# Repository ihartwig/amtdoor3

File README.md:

AMT Door 3
==========

This repository houses hardware for the 3rd generation smart lock at Ace Monster Toys in Berkeley, CA. The hardware and software in this repo plus the PoEPi Hat make a single-cable solution for network connected locks.

</img>

## Features

* Wide Operation Buck Boost and Automation pHat (WOBBApHAT)
  * RPi Zero-sized pHAT
  * bi-directional level shifting for RFID Reader I/O (UART), PWM, and switch inputs (GPIO)
  * 12-24V strike power from on-board boost or aux input
  * (optionally) 5V RPi power from 12-24V source
  * order at http://dirtypcbs.com/store/designer/details/9832/5763/wobbaphat-for-amtdoor3

## Development Structure

* **docs**: Documentation used in designs.
* **pcb**: WOBBApHAT board to connect RPi Zero with RFID Reader and door strike.

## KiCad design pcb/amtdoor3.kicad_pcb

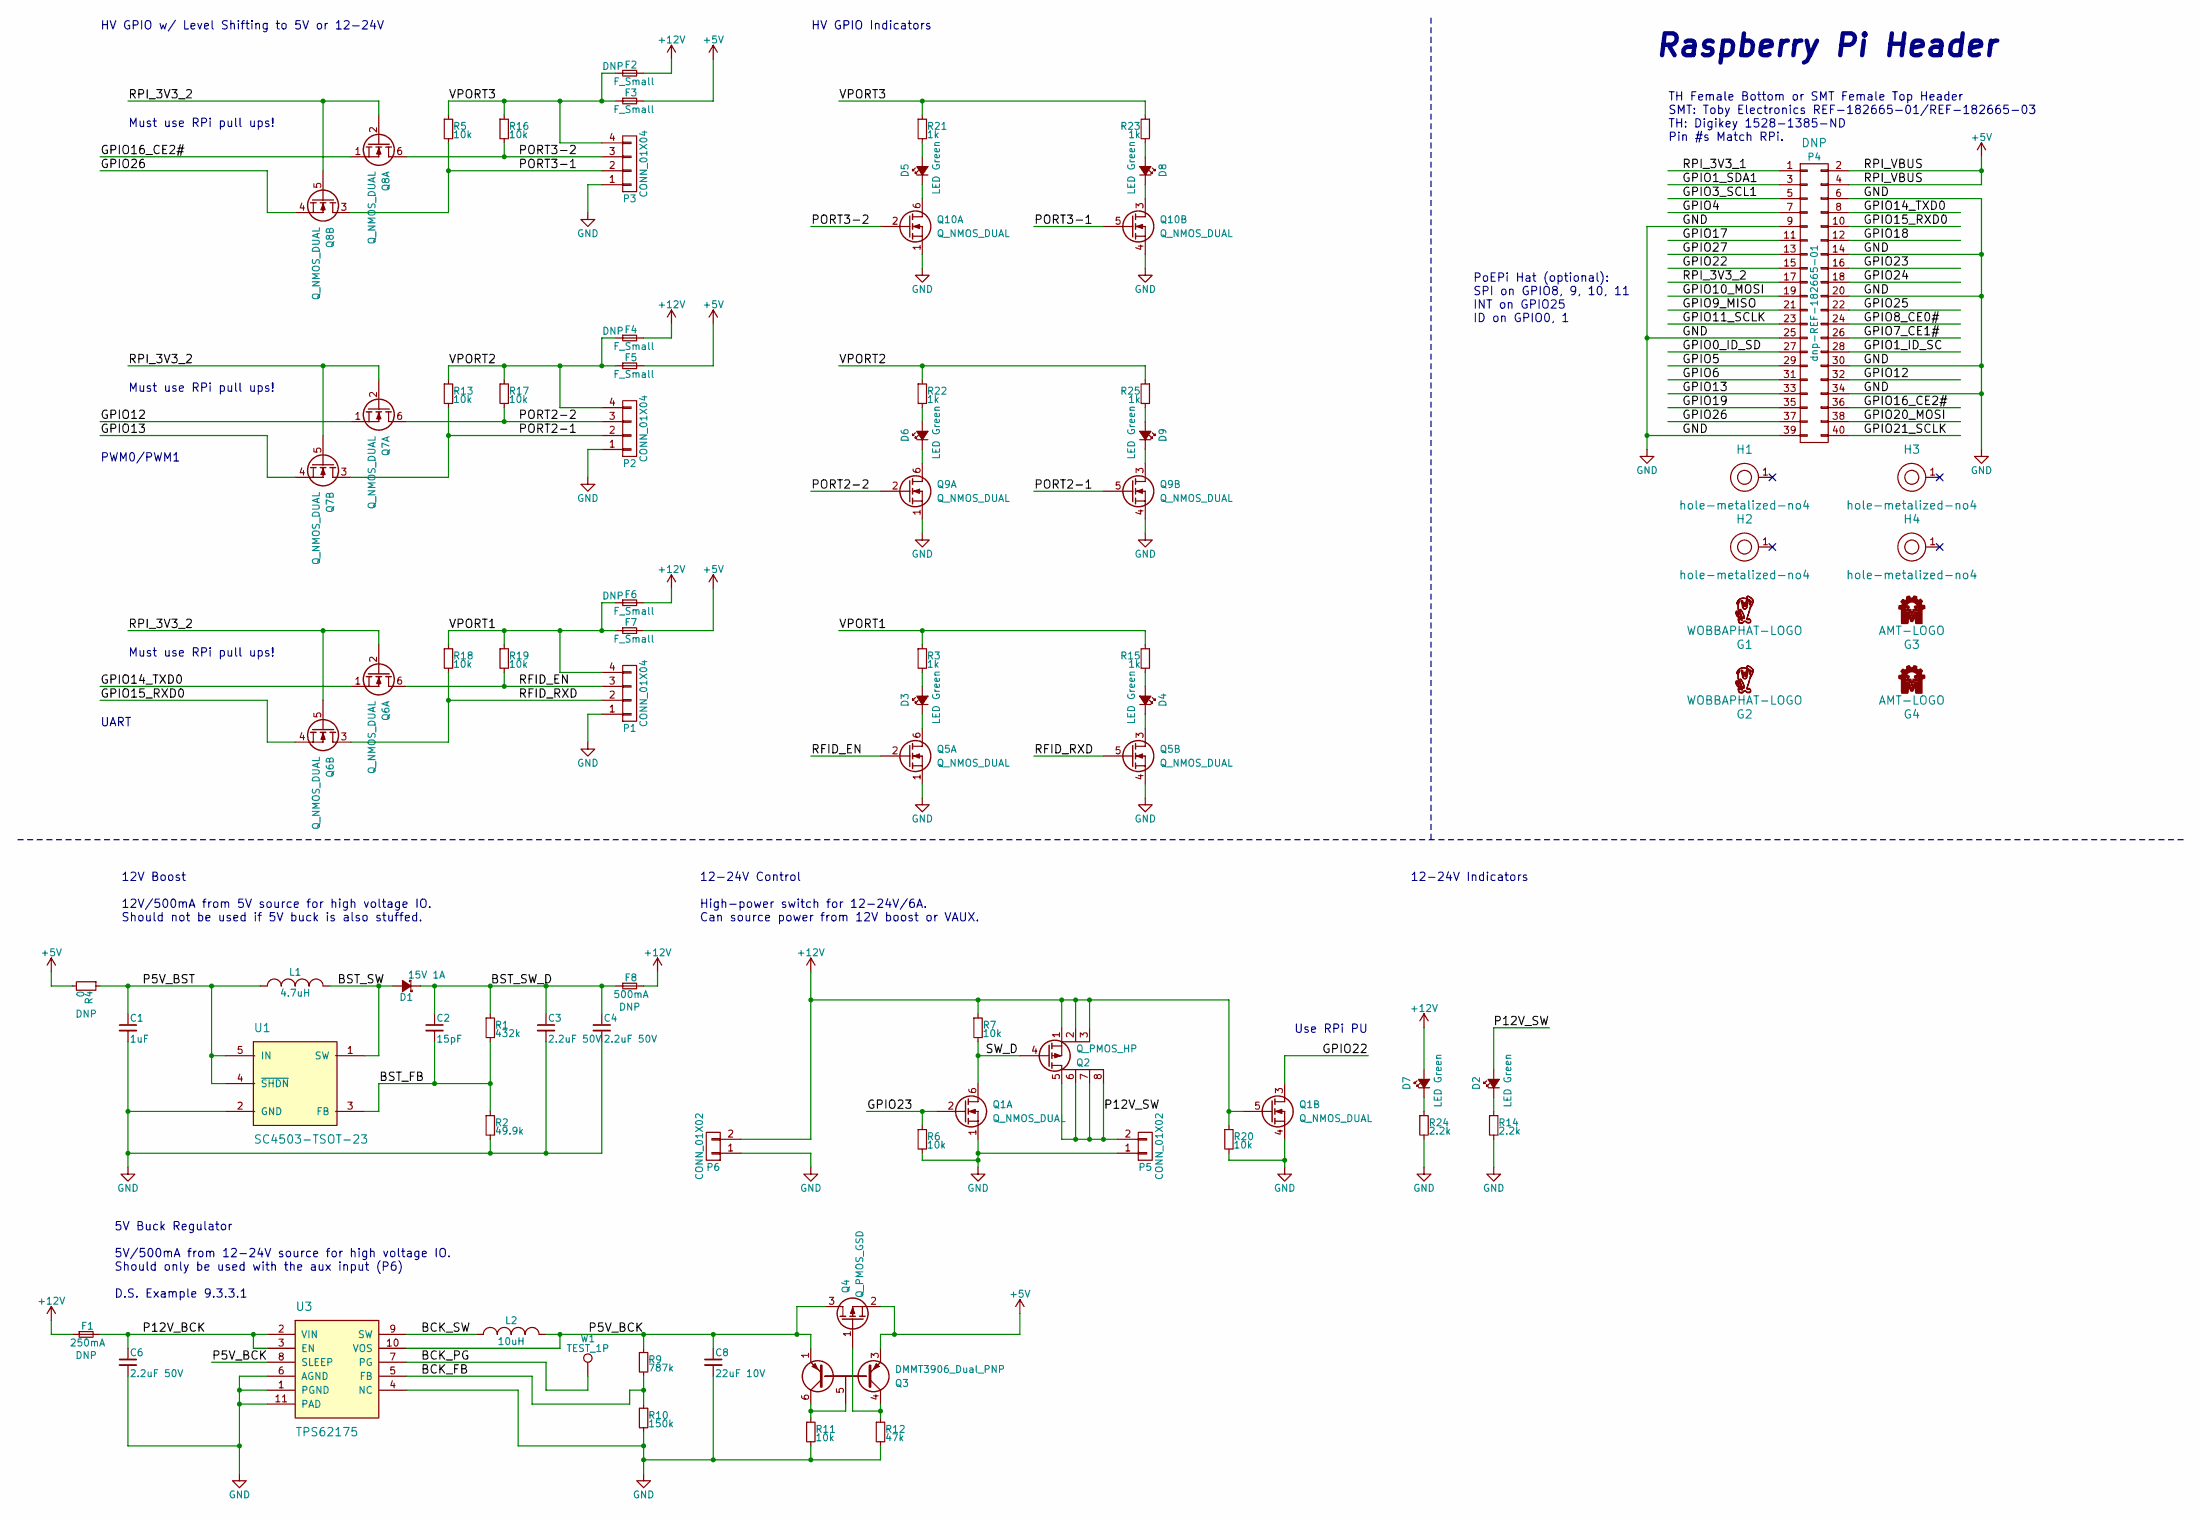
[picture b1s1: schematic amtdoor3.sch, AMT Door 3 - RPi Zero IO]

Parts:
C1: 1uF; C_0603
C2: 15pF; C_0603
C3, C4, C6: 2.2uF 50V; C_0805
C8: 22uF 10V; C_0805
D1: 15V 1A; SMB_Standard; Mfg Part No VS-10BQ015-M3/5BT; Digikey Part No VS-10BQ015-M3/5BTGICT-ND
D2, D3, D4, D5, D6, D7, D8, D9: LED Green; LED_0603; Mfg Part No LTST-C190GKT; Digikey Part No 160-1183-1-ND
F1: 250mA; R_0805
F2, F3, F4, F5, F6, F7: F_Small; R_0603
F8: 500mA; R_0805
G1: WOBBAPHAT-LOGO; wobbaphat-logo-fcu
G2: WOBBAPHAT-LOGO; wobbaphat-logo-fsilk-lg
G3: AMT-LOGO; amt-logo-fcu
G4: AMT-LOGO; amt-logo-fsilk-lg
H1, H2, H3, H4: hole-metalized-no4; hole-m3
L1: 4.7uH; Choke_SMD_Wuerth-WE-PD2-Typ-L; Mfg Part No NR6028T4R7M; Digikey Part No 587-2100-1-ND
L2: 10uH; Choke_SMD_Wuerth-WE-PD2-Typ-L; Mfg Part No NR6045T100M; Digikey Part No 587-2081-1-ND
P1, P2, P3: CONN_01X04; Socket_Strip_Straight_1x04
P4: dnp-REF-182665-01; Pin_Header_Straight_TH-SMT-NoPaste_2x20
P5, P6: CONN_01X02; Pin_Header_Straight_1x02_Pitch3.5mm; Mfg Part No OSTTE020104; Digikey Part No ED2740-ND
Q1, Q5, Q6, Q7, Q8, Q9, Q10: Q_NMOS_DUAL; SOT-23-6
Q2: Q_PMOS_HP; SOIC-8_3.9x4.9mm_Pitch1.27mm; Mfg Part No DMG4435SSS-13; Digikey Part No DMG4435SSS-13DICT-ND
Q3: DMMT3906_Dual_PNP; SOT-23-6; Mfg Part No DMMT3906-7-F; Digikey Part No DMMT3906-7-FDICT-ND
Q4: Q_PMOS_GSD; SOT-23; Mfg Part No DMP3099L-7; Digikey Part No DMP3099L-7DICT-ND
R1: 432k; R_0603
R2: 49.9k; R_0603
R3, R15, R21, R22, R23, R25: 1k; R_0603
R4: 0; R_0603
R5, R6, R7, R11, R13, R16, R17, R18, R19, R20: 10k; R_0603
R9: 787k; R_0603
R10: 150k; R_0603
R12: 47k; R_0603
R14, R24: 2.2k; R_0603
U1: SC4503-TSOT-23; SOT-23-5; Mfg Part No SC4503TSKTRT; Digikey Part No SC4503TSKCT-ND
U3: TPS62175; DFN-10-1EP_2x3mm_Pitch0.5mm; Mfg Part No todo; Digikey Part No todo
W1: TEST_1P; Measurement_Point_Round-SMD-Pad_Small

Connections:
+5V: F3.2, F5.2, F7.2, P4.2, P4.4, Q3.3 (E2), Q4.2 (S), R4.2
+12V: D7.2 (A), F1.1, F2.2, F4.2, F6.2, F8.2, P6.2, Q1.5 (G), Q2.1 (S), Q2.2 (S), Q2.3 (S), R7.1, R20.1
/BCK_FB: R9.2, R10.1, U3.5 (FB)
/BCK_PG: U3.7 (PG), W1.1
/BCK_SW: L2.1, U3.9 (SW)
/BST_FB: C2.2, R1.2, R2.1, U1.3 (FB)
/BST_SW: D1.2 (A), L1.2, U1.1 (SW)
/BST_SW_D: C2.1, C3.1, C4.1, D1.1 (K), F8.1, R1.1
/GPIO0_ID_SD: P4.27
/GPIO1_ID_SC: P4.28
/GPIO1_SDA1: P4.3
/GPIO3_SCL1: P4.5
/GPIO4: P4.7
/GPIO5: P4.29
/GPIO6: P4.31
/GPIO7_CE1#: P4.26
/GPIO8_CE0#: P4.24
/GPIO9_MISO: P4.21
/GPIO10_MOSI: P4.19
/GPIO11_SCLK: P4.23
/GPIO12: P4.32, Q7.1 (S)
/GPIO13: P4.33, Q7.4 (S)
/GPIO14_TXD0: P4.8, Q6.1 (S)
/GPIO15_RXD0: P4.10, Q6.4 (S)
/GPIO16_CE2#: P4.36, Q8.1 (S)
/GPIO17: P4.11
/GPIO18: P4.12
/GPIO19: P4.35
/GPIO20_MOSI: P4.38
/GPIO21_SCLK: P4.40
/GPIO22: P4.15, Q1.3 (D)
/GPIO23: P4.16, Q1.2 (G), R6.1
/GPIO24: P4.18
/GPIO25: P4.22
/GPIO26: P4.37, Q8.4 (S)
/GPIO27: P4.13
/P5V_BCK: C8.1, L2.2, Q3.1 (E1), Q4.3 (D), R9.1, U3.8 (SLEEP), U3.10 (VOS)
/P5V_BST: C1.1, L1.1, R4.1, U1.4 (~SHDN), U1.5 (IN)
/P12V_BCK: C6.1, F1.2, U3.2 (VIN), U3.3 (EN)
/P12V_SW: D2.2 (A), P5.2, Q2.5 (D), Q2.6 (D), Q2.7 (D), Q2.8 (D)
/PORT2-1: P2.2, Q7.3 (D), Q9.5 (G), R13.2
/PORT2-2: P2.3, Q7.6 (D), Q9.2 (G), R17.2
/PORT3-1: P3.2, Q8.3 (D), Q10.5 (G), R5.2
/PORT3-2: P3.3, Q8.6 (D), Q10.2 (G), R16.2
/RFID_EN: P1.3, Q5.2 (G), Q6.6 (D), R19.2
/RFID_RXD: P1.2, Q5.5 (G), Q6.3 (D), R18.2
/RPI_3V3_1: P4.1
/RPI_3V3_2: P4.17, Q6.2 (G), Q6.5 (G), Q7.2 (G), Q7.5 (G), Q8.2 (G), Q8.5 (G)
/SW_D: Q1.6 (D), Q2.4 (G), R7.2
/VPORT1: F6.1, F7.1, P1.4, R3.1, R15.1, R18.1, R19.1
/VPORT2: F4.1, F5.1, P2.4, R13.1, R17.1, R22.1, R25.1
/VPORT3: F2.1, F3.1, P3.4, R5.1, R16.1, R21.1, R23.1
GND: C1.2, C3.2, C4.2, C6.2, C8.2, P1.1, P2.1, P3.1, P4.6, P4.9, P4.14, P4.20, P4.25, P4.30, P4.34, P4.39, P5.1, P6.1, Q1.1 (S), Q1.4 (S), Q5.1 (S), Q5.4 (S), Q9.1 (S), Q9.4 (S), Q10.1 (S), Q10.4 (S), R2.2, R6.2, R10.2, R11.2, R12.2, R14.2, R20.2, R24.2, U1.2 (GND), U3.1 (PGND), U3.4 (NC), U3.6 (AGND), U3.11 (PAD)
unnamed: D2.1 (K), R14.1
unnamed: D3.1 (K), Q5.6 (D)
unnamed: D3.2 (A), R3.2
unnamed: D4.1 (K), Q5.3 (D)
unnamed: D4.2 (A), R15.2
unnamed: D5.1 (K), Q10.6 (D)
unnamed: D5.2 (A), R21.2
unnamed: D6.1 (K), Q9.6 (D)
unnamed: D6.2 (A), R22.2
unnamed: D7.1 (K), R24.1
unnamed: D8.1 (K), Q10.3 (D)
unnamed: D8.2 (A), R23.2
unnamed: D9.1 (K), Q9.3 (D)
unnamed: D9.2 (A), R25.2
unnamed: Q3.4 (C2), Q4.1 (G), R12.1
unnamed: Q3.5 (B), Q3.6 (C1), R11.1

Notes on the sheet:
Raspberry Pi Header
TH Female Bottom or SMT Female Top Header SMT: Toby Electronics REF-182665-01/REF-182665-03 TH: Digikey 1528-1385-ND Pin #s Match RPi.
HV GPIO w/ Level Shifting to 5V or 12-24V
HV GPIO Indicators
12V Boost 12V/500mA from 5V source for high voltage IO. Should not be used if 5V buck is also stuffed.
5V Buck Regulator 5V/500mA from 12-24V source for high voltage IO. Should only be used with the aux input (P6) D.S. Example 9.3.3.1
12-24V Control High-power switch for 12-24V/6A. Can source power from 12V boost or VAUX.
Must use RPi pull ups!
Use RPi PU
12-24V Indicators
UART
PWM0/PWM1
PoEPi Hat (optional): SPI on GPIO8, 9, 10, 11 INT on GPIO25 ID on GPIO0, 1

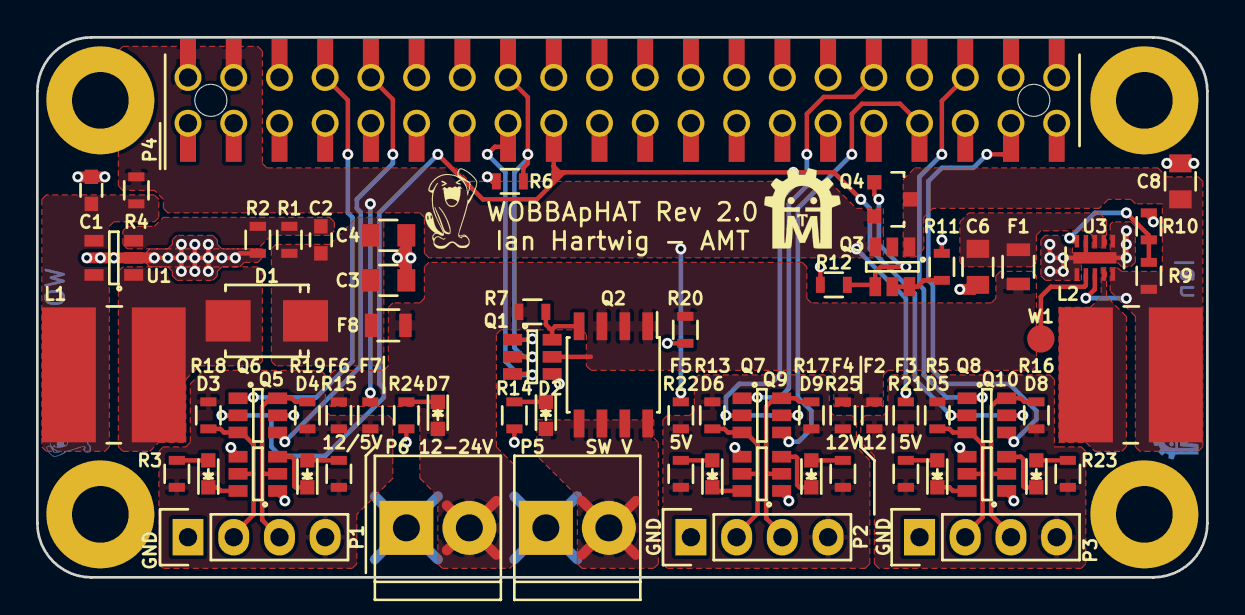
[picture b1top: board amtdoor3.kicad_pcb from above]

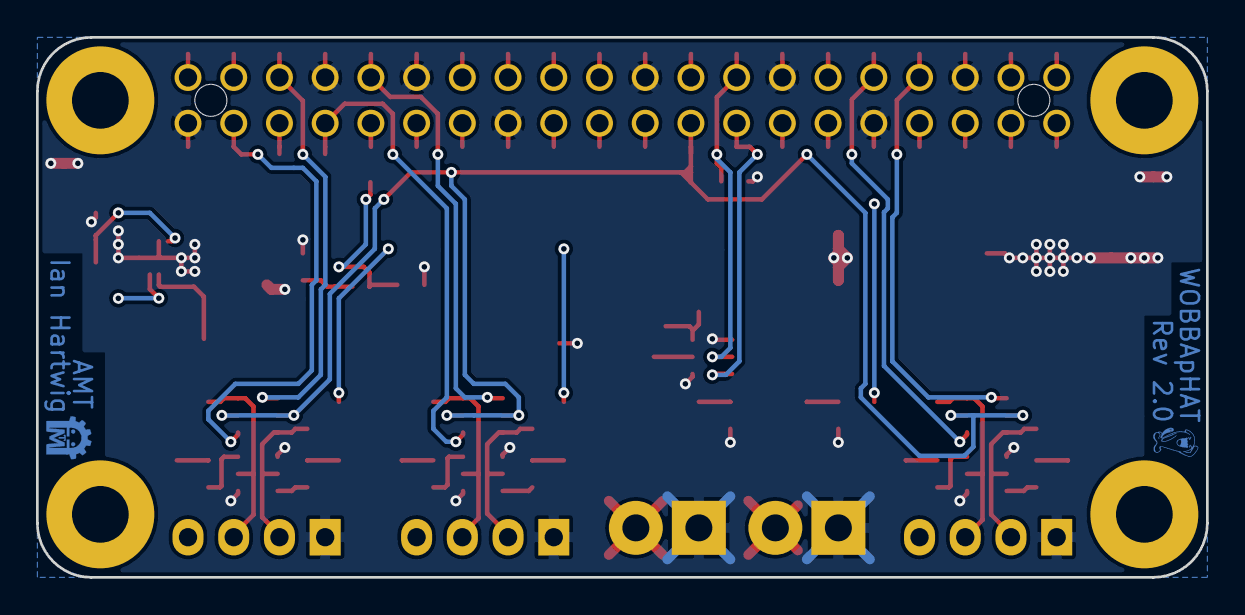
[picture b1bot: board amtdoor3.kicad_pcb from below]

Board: 2 copper layers, 65.0 x 30.0 mm, 76 parts (2 on the bottom side), 48 nets.

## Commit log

2016-10-23 Add pcb with schematic and layout complete
2016-10-23 add readme
2016-10-23 clean up silkscreen, set soldermask expansion, write gerbers
2017-09-24 new rev schematic updates and footprint grouping
    * change level shifter to NFET gates w/ pull up b/c NVT2002 leaks 5V EN to 3.3V rail
    * add selectable, fused output voltage to each port
    * rename P2 to P4 so the output ports are P1, P2, P3
    * use level shifting on all ports
    * reassign GPIO to ports so we have UART TX+RX, PWM, and plain GPIO
    * add fuses and DNPs so boost and buck can be populated but not interfere
2017-09-24 new rev layout complete w/ some sch changes to help routing
    * normalize boost net names
    * fix boost part number to TPS62175. TPS62177 is fixed 3.3V
    * DNP one option for output port voltage
    * fix cap + voltage of boost/buck 12/24V decoupling caps C3, C4, C6
    * reassign GPIO to ports to help routing
2017-09-26 pcb rev 2.0 gerbers, silk logos, routing tweaks
2017-11-24 Add LICENSE

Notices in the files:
pcb/amtdoor3.sch:
License: CERN OHL V1.2
